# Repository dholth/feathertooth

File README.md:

feathertooth
============

Feather form factor (but no USB code upload) SiLabs BGM113 carrier.

USB-C version. Not layed out yet. Need to fix mistakes from previous version:

- No diode to provide USB power if battery not charged
- Many of the BGM113 pins are connected internally, routing
  to the feather pins could be improved

Daniel Holth <dholth@gmail.com>, 2019

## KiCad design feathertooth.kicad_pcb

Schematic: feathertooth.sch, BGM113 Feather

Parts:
C1, C2, C4, C5: C; C_0603
C3: 4.7uF; C_0603
D1, D2: LED; LED_0603
D3: D_Schottky
J1: TopRow; Pin_Header_Straight_1x12_Pitch2.54mm
J2: BottomRow; Pin_Header_Straight_1x16_Pitch2.54mm
J3: BAT; JST-S2B-PH
J4: GT_USB_C; USB_C_Receptacle_GT-USB-7010
J5: Conn_ARM_JTAG_SWD_10; Pin_Header_Straight_2x05_Pitch1.27mm_SMD
MH1, MH2: MountingHole; MountingHole_2.5mm
MH3, MH4: Strap; PINTST
Q1: ? P-CH MOSFET; SOT-23
R1: 10k; R_0603
R2, R3: 470; R_0603
R4: 100k; R_0603
SW1: E_SWITCH
U1: BGM113
U2: MCP1703A; SOT-89-3
U3: MCP73831-2-OT; SOT-23-5

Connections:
+3V3: C2.1, C4.1, C5.1, D2.2, J2.2, J5.1, U1.8, U1.17, U2.3
/Vbat: J1.1, J3.1, Q1.3 (D), U3.3 (VBAT)
/Vusb: C3.1, D1.2, J1.3, J4.A4, J4.A9, J4.B4, J4.B9, Q1.1 (G), R4.1, U3.4 (VDD)
/en: J1.2
/pa0: J2.6, U1.27
/pa0b: U1.23
/pb11: J1.6, R3.2, U1.15
/pb12: J1.7, U1.14
/pb13: J1.8, U1.13
/pc10: J2.11, U1.29
/pc10b: U1.22
/pc11: J2.7, U1.28
/pc11b: U1.21
/pd13: J2.15
/pd14: J2.14, U1.32
/pd15: J2.5, U1.26
/pd15b: U1.24
/pf2: J2.12, U1.30
/pf2b: J5.6, U1.19
/pf3: J2.13, U1.31
/pf3b: U1.20
/rst: J2.1, J5.10, SW1.3, SW1.4, U1.34
/scl: J1.11, U1.12
/sda: J1.12, U1.11
/swdclk: J1.9, J5.4, U1.10
/swdio: J1.10, J5.2, U1.9
GND: C1.2, C2.2, C3.2, C4.2, C5.2, J2.4, J2.16, J3.2, J4.A1, J4.A12, J4.B1, J4.B12, J4.S1, J5.3, J5.5, R1.2, R4.2, SW1.1, SW1.2, U1.1, U1.2, U1.3, U1.4, U1.5, U1.6, U1.7, U1.18, U1.25, U1.36, U2.1, U3.2 (VSS)
unnamed: C1.1, U2.2
unnamed: D1.1, R2.1
unnamed: D2.1, R3.1
unnamed: R1.1, U3.5 (PROG)
unnamed: R2.2, U3.1 (STAT)

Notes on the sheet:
bat
decoupling
MCP AN1149

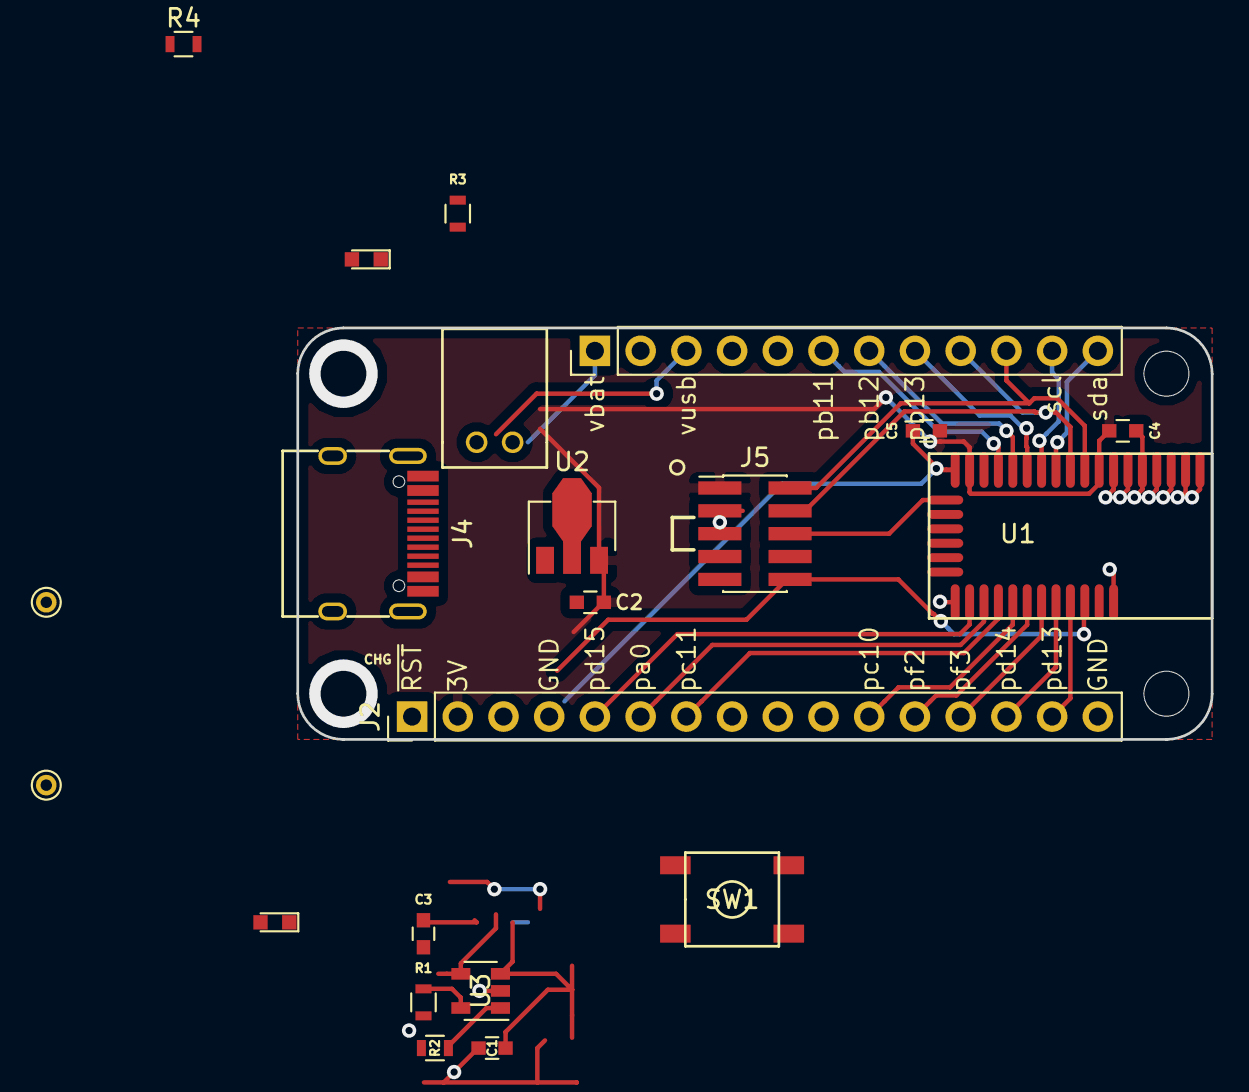
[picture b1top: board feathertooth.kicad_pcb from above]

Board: 2 copper layers, 50.8 x 22.9 mm, 24 parts (0 on the bottom side), 25 nets.

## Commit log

2019-09-19 Feather form factor BGM113 board
2019-09-19 unfinished USB-C second revision
2019-09-19 add board render
2019-09-19 usb-c version render
